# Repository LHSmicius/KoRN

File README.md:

# KoRN
Key to Reshape Norms

A new look at how the keyboard may look like.

Download footprints for mechanical switches from https://github.com/daprice/keyswitches.pretty
```shell
cd kicad-footprints
git clone git@github.com:daprice/keyswitches.pretty.git
```

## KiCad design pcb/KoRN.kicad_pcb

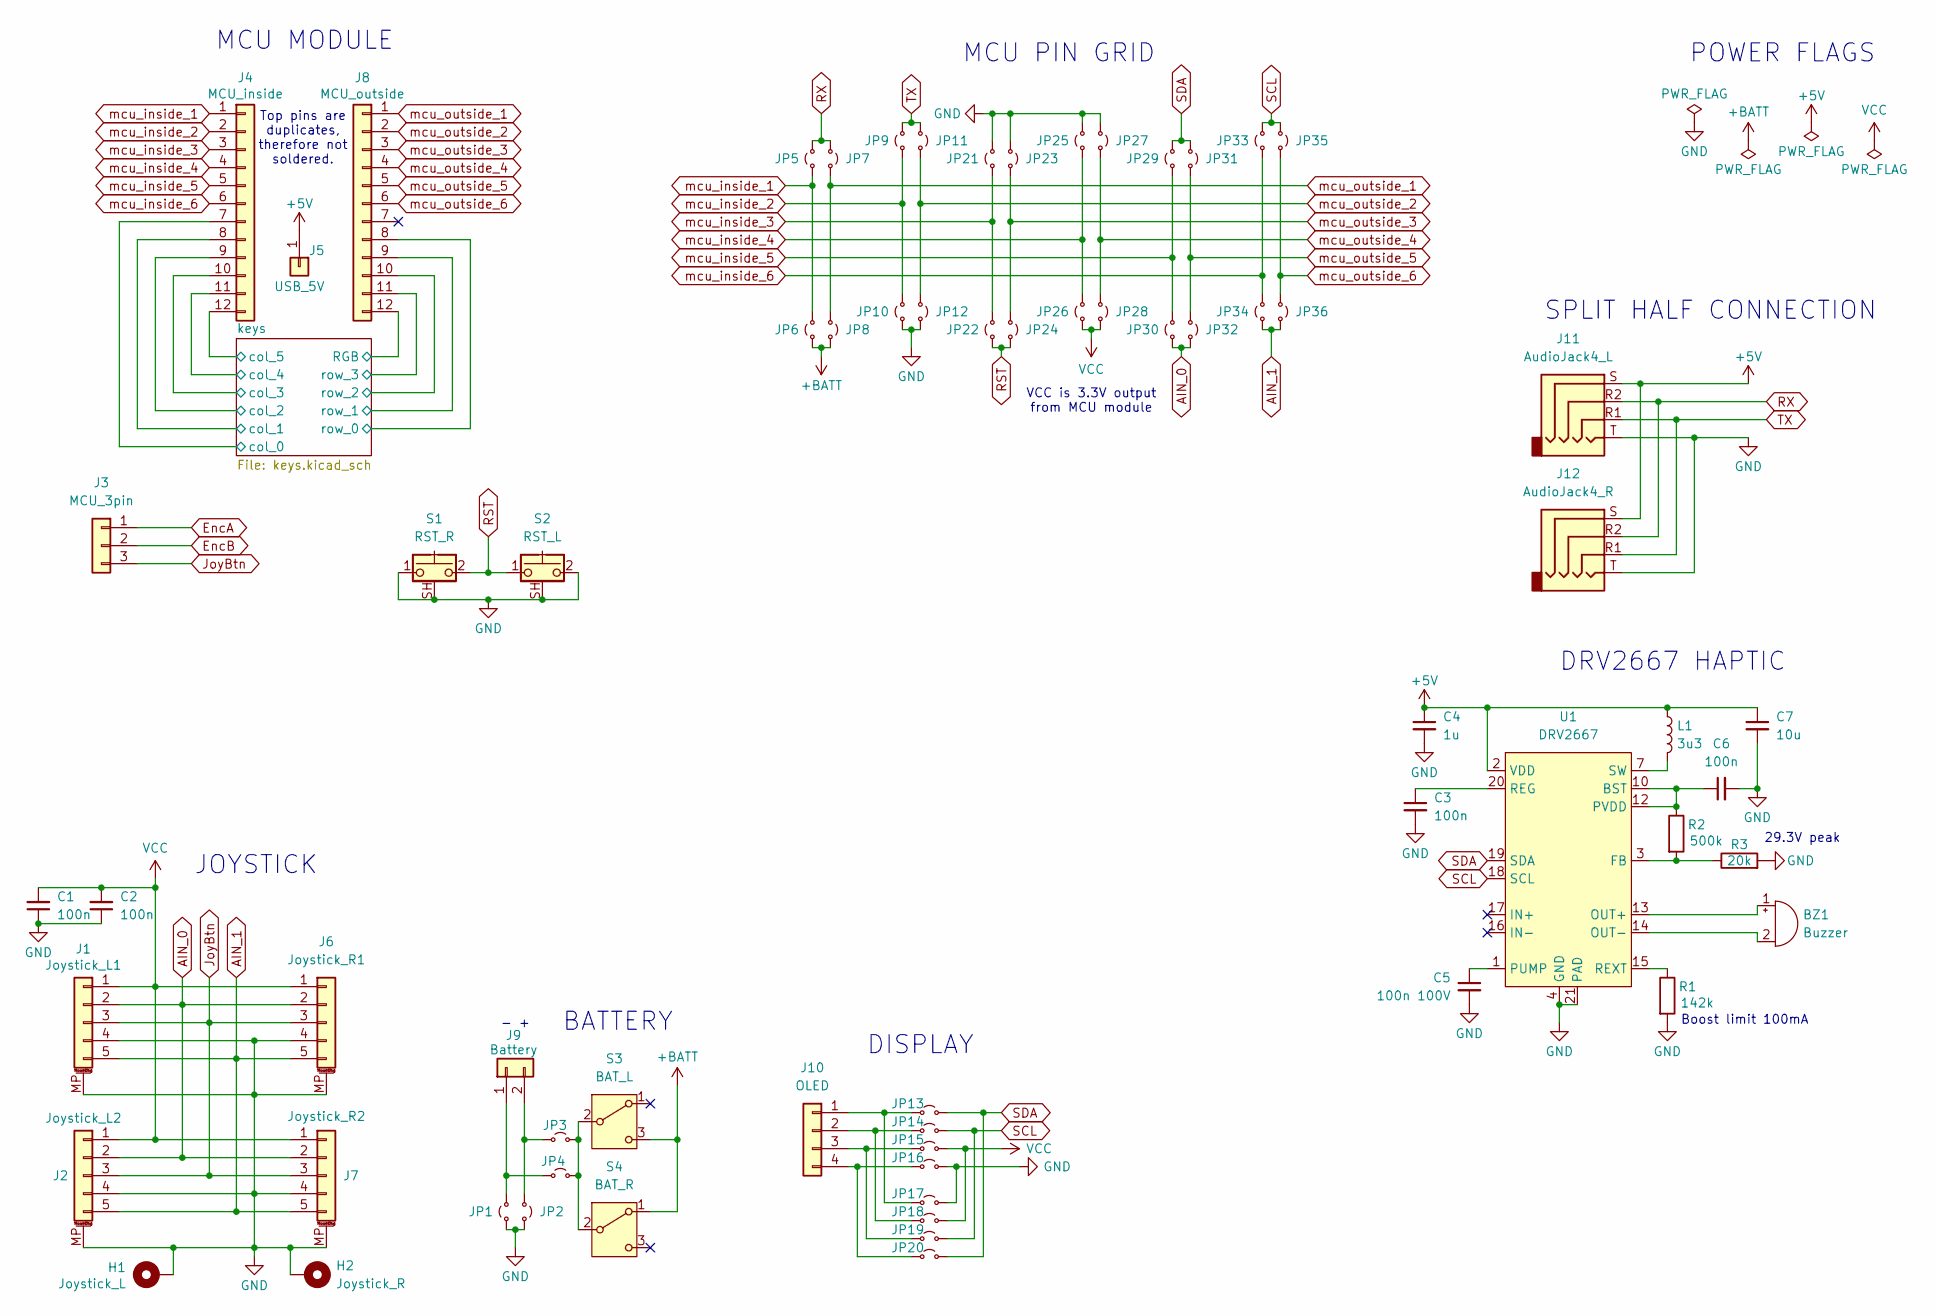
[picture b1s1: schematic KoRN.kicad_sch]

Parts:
BZ1: Buzzer; PiezoDisc_15mm_12mm
C1, C2, C3, C6: 100n; C_0805_2012Metric
C4: 1u; C_0805_2012Metric
C5: 100n 100V; C_0805_2012Metric
C7: 10u; C_1206_3216Metric
H1: Joystick_L; Joystick_nintendo_switch
H2: Joystick_R; Joystick_nintendo_switch
J1: Joystick_L1; Amphenol_F32Q-1A7x1-11005_1x05-1MP_P0.5mm_Horizontal
J2: Joystick_L2; Amphenol_F32Q-1A7x1-11005_1x05-1MP_P0.5mm_Horizontal
J3: MCU_3pin; ProMicro_3pin
J4: MCU_inside; PinSocket_1x12_P2.54mm_Vertical
J5: USB_5V; Pin_D0.7mm_L6.5mm_W1.8mm_FlatFork
J6: Joystick_R1; Amphenol_F32Q-1A7x1-11005_1x05-1MP_P0.5mm_Horizontal
J7: Joystick_R2; Amphenol_F32Q-1A7x1-11005_1x05-1MP_P0.5mm_Horizontal
J8: MCU_outside; PinSocket_1x12_P2.54mm_Vertical
J9: Battery; JST_PH_S2B-PH-K_1x02_P2.00mm_Horizontal
J10: OLED; PinSocket_1x04_P2.54mm_Vertical
J11: AudioJack4_L; Jack_3.5mm_PJ320D_Horizontal
J12: AudioJack4_R; Jack_3.5mm_PJ320D_Horizontal
JP1: GND_bat_R; SolderJumper
JP2: GND_bat_L; SolderJumper
JP3: Plus_bat_R; SolderJumper
JP4: Plus_bat_L; SolderJumper
JP5: RX_L; SolderJumper
JP6: BAT_R; SolderJumper
JP7: RX_R; SolderJumper
JP8: BAT_L; SolderJumper
JP9: TX_L; SolderJumper
JP10: GND2_R; SolderJumper
JP11: TX_R; SolderJumper
JP12: GND2_L; SolderJumper
JP13: OLED_SDA_L; SolderJumper
JP14: OLED_SCL_L; SolderJumper
JP15: OLED_VCC_L; SolderJumper
JP16: OLED_GND_L; SolderJumper
JP17: OLED_GND_R; SolderJumper
JP18: OLED_VCC_R; SolderJumper
JP19: OLED_SCL_R; SolderJumper
JP20: OLED_SDA_R; SolderJumper
JP21: GND3_L; SolderJumper
JP22: RST_R; SolderJumper
JP23: GND3_R; SolderJumper
JP24: RST_L; SolderJumper
JP25: GND4_L; SolderJumper
JP26: VCC_R; SolderJumper
JP27: GND4_R; SolderJumper
JP28: VCC_L; SolderJumper
JP29: SDA_L; SolderJumper
JP30: AIN0_R; SolderJumper
JP31: SDA_R; SolderJumper
JP32: AIN0_L; SolderJumper
JP33: SCL_L; SolderJumper
JP34: AIN1_R; SolderJumper
JP35: SCL_R; SolderJumper
JP36: AIN1_L; SolderJumper
L1: 3u3; L_APV_APH0518
R1: 142k; R_0603_1608Metric
R2: 500k; R_0603_1608Metric
R3: 20k; R_0603_1608Metric
S1: RST_R; ResetButton
S2: RST_L; ResetButton
S3: BAT_L; SW_SPDT_PCM12
S4: BAT_R; SW_SPDT_PCM12
U1: DRV2667; QFN-20-1EP_4x4mm_P0.5mm_EP2.7x2.7mm_ThermalVias

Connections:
+5V: C4.1, C7.1, J5.1 (Pin_1_1), J11.S, J12.S, L1.1, U1.2 (VDD)
+BATT: JP6.1 (A), JP8.2 (B), S3.3 (C), S4.1 (A)
/keys/RGB: J8.12; also elsewhere on the board
/keys/col_0: J4.7; also elsewhere on the board
/keys/col_1: J4.8; also elsewhere on the board
/keys/col_2: J4.9; also elsewhere on the board
/keys/col_3: J4.10; also elsewhere on the board
/keys/col_4: J4.11; also elsewhere on the board
/keys/col_5: J4.12; also elsewhere on the board
/keys/row_0: J8.8; also elsewhere on the board
/keys/row_1: J8.9; also elsewhere on the board
/keys/row_2: J8.10; also elsewhere on the board
/keys/row_3: J8.11; also elsewhere on the board
AIN_0: J1.2, J2.2, J6.2, J7.2, JP30.1 (A), JP32.2 (B)
AIN_1: J1.5, J2.5, J6.5, J7.5, JP34.1 (A), JP36.2 (B)
EncA: J3.1; also elsewhere on the board
EncB: J3.2; also elsewhere on the board
GND: C1.1, C2.1, C3.2, C4.2, C5.2, C6.2, C7.2, H1.MP (MP_MP), H2.MP (MP_MP), J1.4, J1.MP (MountPin), J2.4, J2.MP (MountPin), J6.4, J6.MP (MountPin), J7.4, J7.MP (MountPin), J11.T, J12.T, JP1.1 (A), JP2.2 (B), JP10.1 (A), JP12.2 (B), JP16.2 (B), JP17.2 (B), JP21.2 (B), JP23.1 (A), JP25.2 (B), JP27.1 (A), R1.2, R3.2, S1.1, S1.SH (B), S2.2, S2.SH (B), U1.4 (GND), U1.5 (GND), U1.6 (GND), U1.21 (PAD); also elsewhere on the board
JoyBtn: J1.3, J2.3, J3.3, J6.3, J7.3
unnamed: BZ1.1 (+), U1.13 (OUT+)
unnamed: BZ1.2 (-), U1.14 (OUT-)
unnamed: J9.1, JP1.2 (B), JP4.1 (A)
unnamed: J9.2, JP2.1 (A), JP3.1 (A)
unnamed: J10.1, JP13.1 (A), JP17.1 (A)
unnamed: J10.2, JP14.1 (A), JP18.1 (A)
unnamed: J10.3, JP15.1 (A), JP19.1 (A)
unnamed: J10.4, JP16.1 (A), JP20.1 (A)
unnamed: JP3.2 (B), JP4.2 (B), S3.2 (B), S4.2 (B)
unnamed: L1.2, U1.7 (SW), U1.8 (SW)
unnamed: R2.2, R3.1, U1.3 (FB)
unnamed: C5.1, U1.1 (PUMP)
unnamed: C6.1, R2.1, U1.10 (BST), U1.11 (BST), U1.12 (PVDD)
unnamed: C3.1, U1.20 (REG)
unnamed: R1.1, U1.15 (REXT)
RST: JP22.1 (A), JP24.2 (B), S1.2, S2.1
RX: J11.R2, J12.R2, JP5.2 (B), JP7.1 (A)
SCL: JP14.2 (B), JP19.2 (B), JP33.2 (B), JP35.1 (A), U1.18 (SCL)
SDA: JP13.2 (B), JP20.2 (B), JP29.2 (B), JP31.1 (A), U1.19 (SDA)
TX: J11.R1, J12.R1, JP9.2 (B), JP11.1 (A)
VCC: C1.2, C2.2, J1.1, J2.1, J6.1, J7.1, JP15.2 (B), JP18.2 (B), JP26.1 (A), JP28.2 (B); also elsewhere on the board
mcu_inside_1: J4.1, JP5.1 (A), JP6.2 (B)
mcu_inside_2: J4.2, JP9.1 (A), JP10.2 (B)
mcu_inside_3: J4.3, JP21.1 (A), JP22.2 (B)
mcu_inside_4: J4.4, JP25.1 (A), JP26.2 (B)
mcu_inside_5: J4.5, JP29.1 (A), JP30.2 (B)
mcu_inside_6: J4.6, JP33.1 (A), JP34.2 (B)
mcu_outside_1: J8.1, JP7.2 (B), JP8.1 (A)
mcu_outside_2: J8.2, JP11.2 (B), JP12.1 (A)
mcu_outside_3: J8.3, JP23.2 (B), JP24.1 (A)
mcu_outside_4: J8.4, JP27.2 (B), JP28.1 (A)
mcu_outside_5: J8.5, JP31.2 (B), JP32.1 (A)
mcu_outside_6: J8.6, JP35.2 (B), JP36.1 (A)

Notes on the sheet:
JOYSTICK
MCU PIN GRID
- +
DISPLAY
SPLIT HALF CONNECTION
DRV2667 HAPTIC
Top pins are duplicates, therefore not soldered.
VCC is 3.3V output from MCU module
POWER FLAGS
Boost limit 100mA
MCU MODULE
BATTERY
29.3V peak

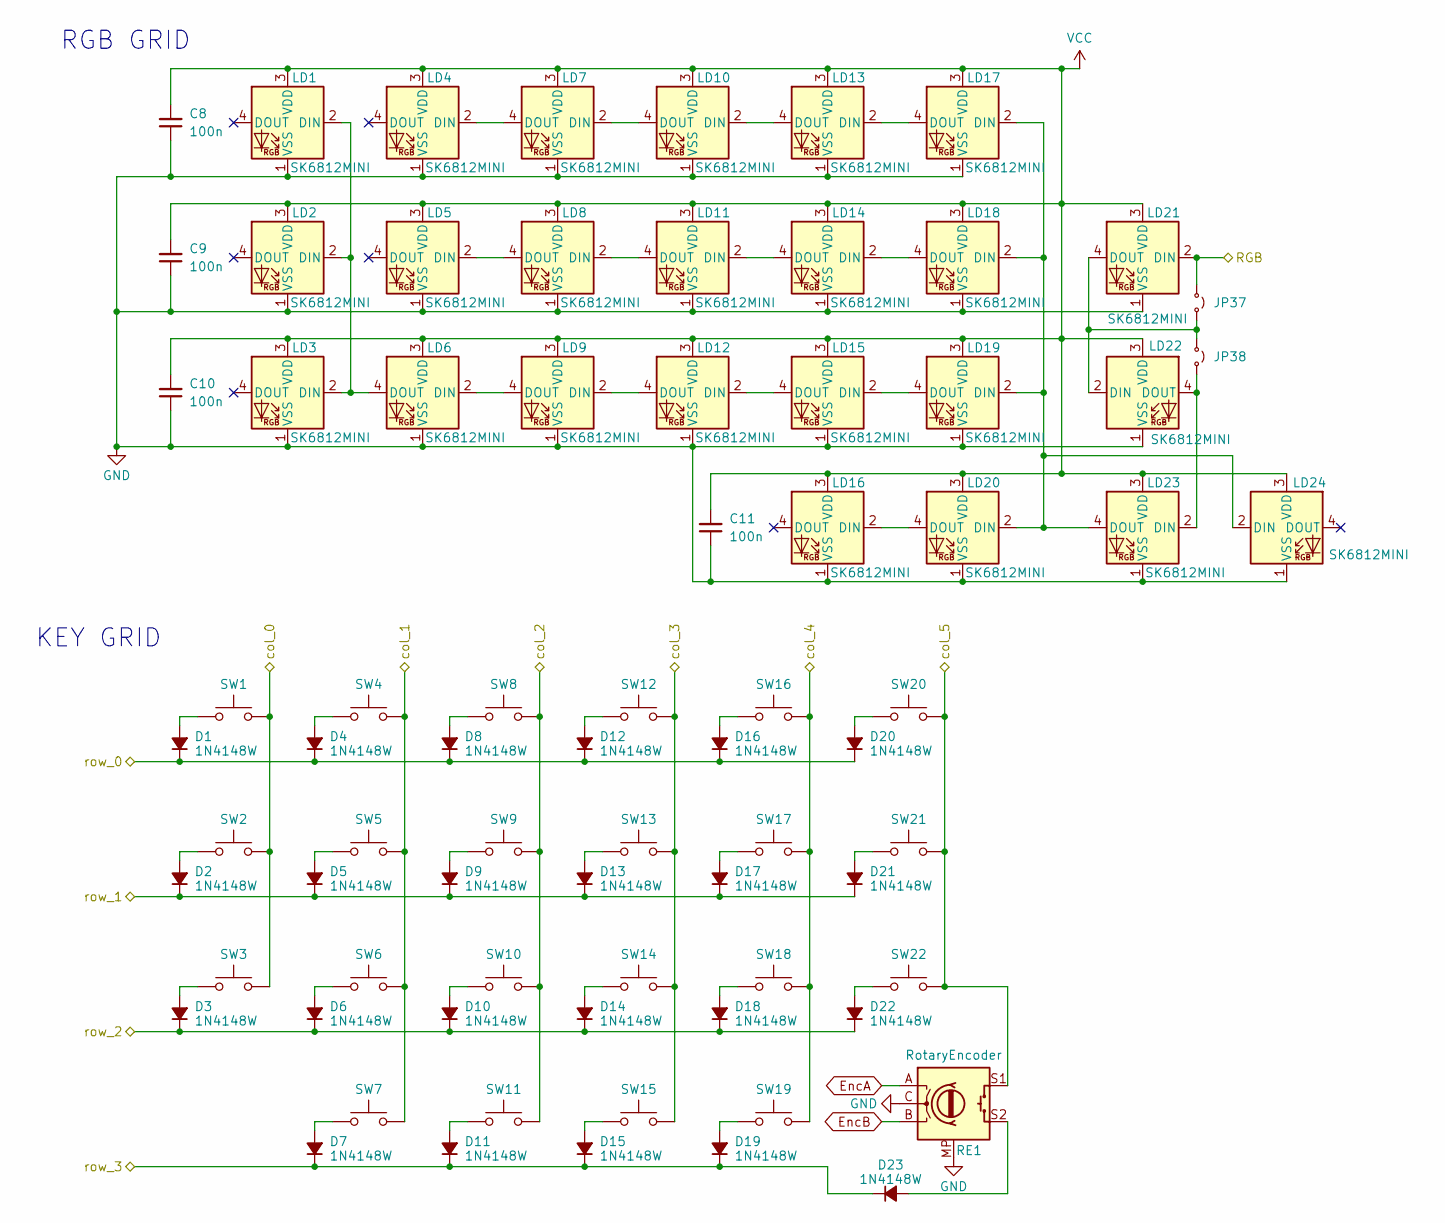
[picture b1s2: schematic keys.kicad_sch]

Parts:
C8, C9, C10, C11: 100n; C_0805_2012Metric
D1, D2, D3, D4, D5, D6, D7, D8, D9, D10, D11, D12, D13, D14, D15, D16, D17, D18, D19, D20, D21, D22, D23: 1N4148W; D_SOD-123
JP37: EncTop; SolderJumper
JP38: EncBot; SolderJumper
LD1, LD2, LD3, LD4, LD5, LD6, LD7, LD8, LD9, LD10, LD11, LD12, LD13, LD14, LD15, LD16, LD17, LD18, LD19, LD20, LD21, LD22, LD23, LD24: SK6812MINI; SK6812_mini-e_rgb_reversible
RE1: RotaryEncoder; RotaryEncoder_Alps_EC11E-Switch_Vertical_H20mm
SW1, SW2, SW3, SW4, SW5, SW6, SW7, SW8, SW9, SW10, SW11, SW12, SW13, SW14, SW15, SW16, SW17, SW18, SW19, SW20, SW21, SW22: SW_Push; Kailh_socket_PG1350_reversible

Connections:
/keys/RGB: JP37.1 (A), LD21.2 (DIN); also elsewhere on the board
/keys/col_0: SW1.2, SW2.2, SW3.2; also elsewhere on the board
/keys/col_1: SW4.2, SW5.2, SW6.2, SW7.2; also elsewhere on the board
/keys/col_2: SW8.2, SW9.2, SW10.2, SW11.2; also elsewhere on the board
/keys/col_3: SW12.2, SW13.2, SW14.2, SW15.2; also elsewhere on the board
/keys/col_4: SW16.2, SW17.2, SW18.2, SW19.2; also elsewhere on the board
/keys/col_5: RE1.S1, SW20.2, SW21.2, SW22.2; also elsewhere on the board
/keys/row_0: D1.1 (K), D4.1 (K), D8.1 (K), D12.1 (K), D16.1 (K), D20.1 (K); also elsewhere on the board
/keys/row_1: D2.1 (K), D5.1 (K), D9.1 (K), D13.1 (K), D17.1 (K), D21.1 (K); also elsewhere on the board
/keys/row_2: D3.1 (K), D6.1 (K), D10.1 (K), D14.1 (K), D18.1 (K), D22.1 (K); also elsewhere on the board
/keys/row_3: D7.1 (K), D11.1 (K), D15.1 (K), D19.1 (K), D23.1 (K); also elsewhere on the board
EncA: RE1.A; also elsewhere on the board
EncB: RE1.B; also elsewhere on the board
GND: C8.1, C9.1, C10.1, C11.1, LD1.1 (VSS), LD2.1 (VSS), LD3.1 (VSS), LD4.1 (VSS), LD5.1 (VSS), LD6.1 (VSS), LD7.1 (VSS), LD8.1 (VSS), LD9.1 (VSS), LD10.1 (VSS), LD11.1 (VSS), LD12.1 (VSS), LD13.1 (VSS), LD14.1 (VSS), LD15.1 (VSS), LD16.1 (VSS), LD17.1 (VSS), LD18.1 (VSS), LD19.1 (VSS), LD20.1 (VSS), LD21.1 (VSS), LD22.1 (VSS), LD23.1 (VSS), LD24.1 (VSS), RE1.C, RE1.MP; also elsewhere on the board
unnamed: D1.2 (A), SW1.1
unnamed: D2.2 (A), SW2.1
unnamed: D3.2 (A), SW3.1
unnamed: D4.2 (A), SW4.1
unnamed: D5.2 (A), SW5.1
unnamed: D6.2 (A), SW6.1
unnamed: D7.2 (A), SW7.1
unnamed: D8.2 (A), SW8.1
unnamed: D9.2 (A), SW9.1
unnamed: D10.2 (A), SW10.1
unnamed: D11.2 (A), SW11.1
unnamed: D12.2 (A), SW12.1
unnamed: D13.2 (A), SW13.1
unnamed: D14.2 (A), SW14.1
unnamed: D15.2 (A), SW15.1
unnamed: D16.2 (A), SW16.1
unnamed: D17.2 (A), SW17.1
unnamed: D18.2 (A), SW18.1
unnamed: D19.2 (A), SW19.1
unnamed: D20.2 (A), SW20.1
unnamed: D21.2 (A), SW21.1
unnamed: D22.2 (A), SW22.1
unnamed: D23.2 (A), RE1.S2
unnamed: JP37.2 (B), JP38.1 (A), LD21.4 (DOUT), LD22.2 (DIN)
unnamed: JP38.2 (B), LD22.4 (DOUT), LD23.2 (DIN)
unnamed: LD1.2 (DIN), LD2.2 (DIN), LD3.2 (DIN), LD6.4 (DOUT)
unnamed: LD4.2 (DIN), LD7.4 (DOUT)
unnamed: LD5.2 (DIN), LD8.4 (DOUT)
unnamed: LD6.2 (DIN), LD9.4 (DOUT)
unnamed: LD10.2 (DIN), LD13.4 (DOUT)
unnamed: LD7.2 (DIN), LD10.4 (DOUT)
unnamed: LD11.2 (DIN), LD14.4 (DOUT)
unnamed: LD8.2 (DIN), LD11.4 (DOUT)
unnamed: LD12.2 (DIN), LD15.4 (DOUT)
unnamed: LD9.2 (DIN), LD12.4 (DOUT)
unnamed: LD13.2 (DIN), LD17.4 (DOUT)
unnamed: LD14.2 (DIN), LD18.4 (DOUT)
unnamed: LD15.2 (DIN), LD19.4 (DOUT)
unnamed: LD16.2 (DIN), LD20.4 (DOUT)
unnamed: LD17.2 (DIN), LD18.2 (DIN), LD19.2 (DIN), LD20.2 (DIN), LD23.4 (DOUT), LD24.2 (DIN)
VCC: C8.2, C9.2, C10.2, C11.2, LD1.3 (VDD), LD2.3 (VDD), LD3.3 (VDD), LD4.3 (VDD), LD5.3 (VDD), LD6.3 (VDD), LD7.3 (VDD), LD8.3 (VDD), LD9.3 (VDD), LD10.3 (VDD), LD11.3 (VDD), LD12.3 (VDD), LD13.3 (VDD), LD14.3 (VDD), LD15.3 (VDD), LD16.3 (VDD), LD17.3 (VDD), LD18.3 (VDD), LD19.3 (VDD), LD20.3 (VDD), LD21.3 (VDD), LD22.3 (VDD), LD23.3 (VDD), LD24.3 (VDD); also elsewhere on the board

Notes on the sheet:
KEY GRID
RGB GRID

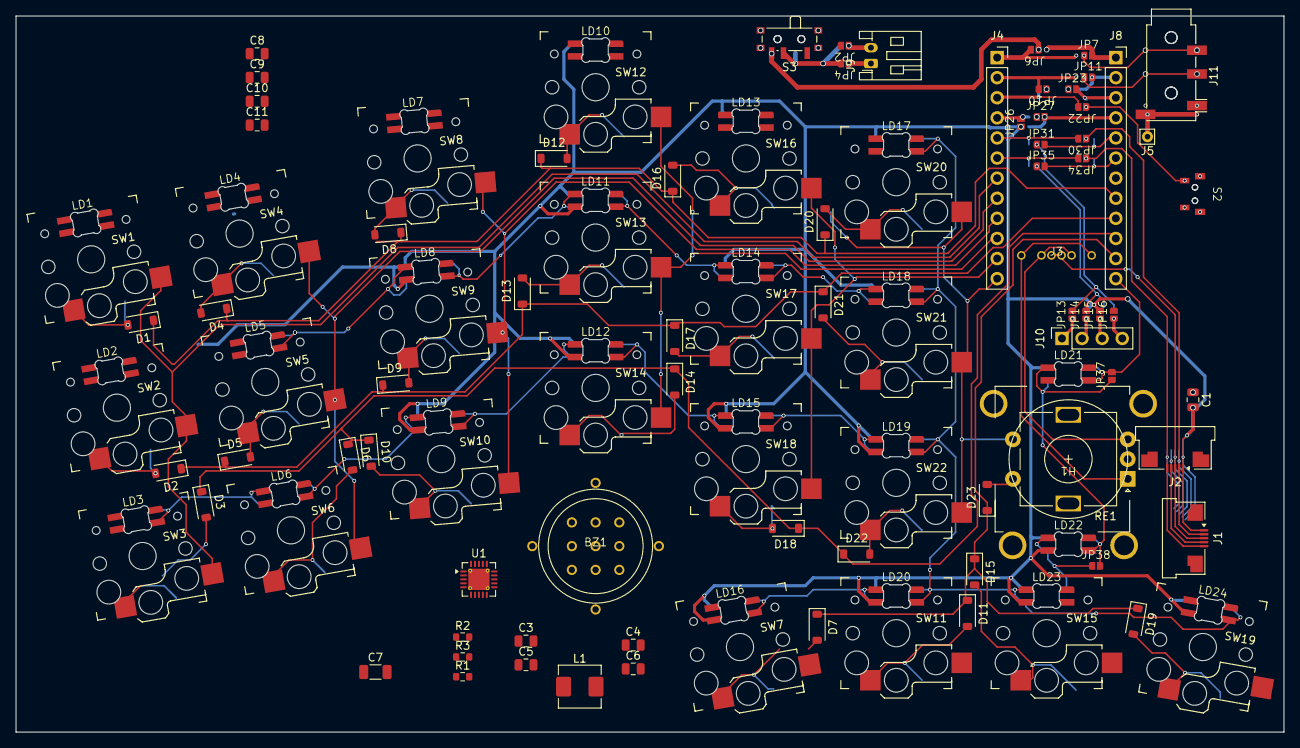
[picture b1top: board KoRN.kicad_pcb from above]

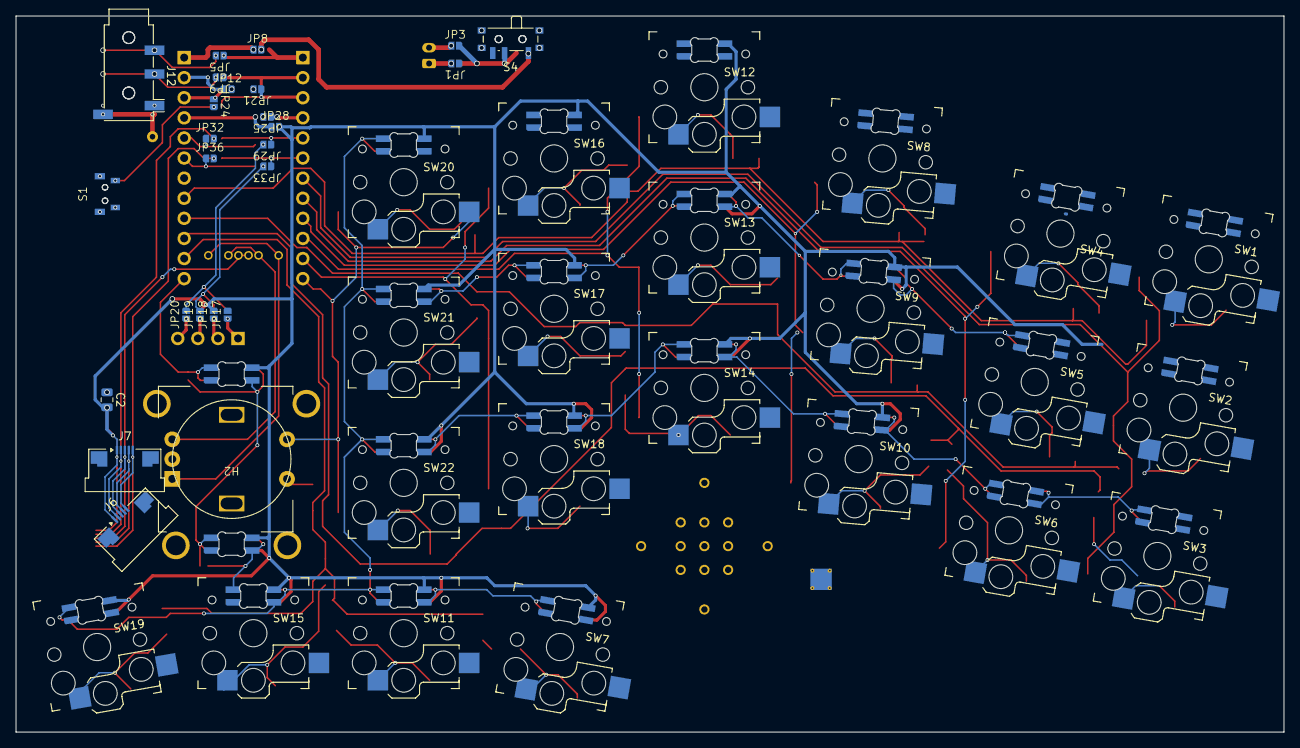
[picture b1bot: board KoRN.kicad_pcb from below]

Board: 2 copper layers, 160.2 x 90.5 mm, 143 parts (25 on the bottom side), 92 nets.
